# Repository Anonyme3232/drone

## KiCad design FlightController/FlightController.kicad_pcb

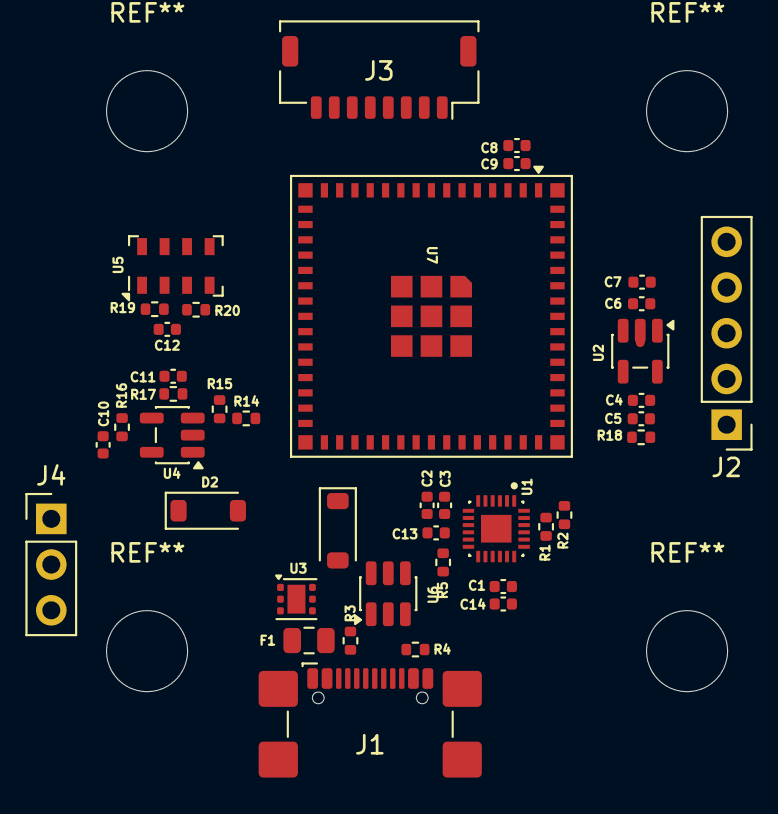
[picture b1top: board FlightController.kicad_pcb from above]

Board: 2 copper layers, 40 parts (0 on the bottom side), 31 nets.

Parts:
C1, C2: 10nF; C_0402_1005Metric
C3, C9, C13, C14: 100nF; C_0402_1005Metric
C4, C6: 1uF; C_0402_1005Metric
C5, C7, C8: 10uF; C_0402_1005Metric
C10: 22uF; C_0402_1005Metric
C11: 15nF; C_0402_1005Metric
C12: 0.1uF; C_0402_1005Metric
D1, D2: D_Schottky; D_SOD-123
F1: Polyfuse_Small; Fuse_0805_2012Metric
J1: USB_C_Receptacle_USB2.0_16P; USB_C_Receptacle_GCT_USB4110
J2: Conn_01x05; PinHeader_1x05_P2.54mm_Vertical
J3: Conn_01x08; JST_SHL_SM08B-SHLS-TF_1x08-1MP_P1.00mm_Horizontal
J4: Conn_01x03; PinHeader_1x03_P2.54mm_Vertical
R1, R2: 10k; R_0402_1005Metric
R3, R4, R18: 5.1K; R_0402_1005Metric
R5, R14, R15: 10K; R_0402_1005Metric
R16, R19, R20: 1K; R_0402_1005Metric
R17: 100K; R_0402_1005Metric
U1: MPU-6500; MPU6500
U2: AP2112K-3.3; SOT-23-5
U3: TVS0500DRV; WSON-6-1EP_2x2mm_P0.65mm_EP1x1.6mm
U4: MCP6001R; SOT-23-5
U5: MS5611-01BA; LGA-8_3x5mm_P1.25mm
U6: USBLC6-2SC6; SOT-23-6
U7: ESP32-S3-MINI-1U; ESP32-S2-MINI-1U

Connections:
/HB100/3V3: R14.1, U4.2 (V+)
/HB100/GPIO1: C11.2, R17.1, U4.1
/Raíz/3V3: C4.1, C5.1, C8.2, C9.2, C12.1, J2.1, R1.1, R2.1, R18.2, R19.1, U1.22 (NCS), U2.5 (VOUT), U5.1 (VDD), U7.3 (3V3)
/Raíz/5V: C6.1, C7.1, D1.1 (K), D2.1 (K), U2.1 (VIN), U2.3 (EN)
/Raíz/D+: U6.4 (I/O2), U7.24 (USB_D+)
/Raíz/D-: U6.6 (I/O1), U7.23 (USB_D-)
/Raíz/INT: R5.1, U1.12 (INT), U7.30 (IO48)
/Raíz/M1_R: J3.6, U7.19 (IO15)
/Raíz/M2_R: J3.5, U7.20 (IO16)
/Raíz/M3_R: J3.4, U7.21 (IO17)
/Raíz/M4_R: J3.3, U7.22 (IO18)
/Raíz/SCL: U5.8 (SCLK), U7.31 (IO35)
/Raíz/SDA: U5.7 (SDI/SDA), U7.32 (IO36)
/Raíz/VDDIO: C2.1, C3.2, U1.8 (VDDIO)
GND: C1.2, C2.2, C3.1, C4.2, C5.2, C6.2, C7.2, C8.1, C9.1, C12.2, C13.1, C14.1, F1.1, J1.A1 (GND), J1.A12 (GND), J1.B1 (GND), J1.B12 (GND), J1.SH (SHIELD), J2.4, J3.8, J4.3, R3.2, R4.2, R5.2, R15.1, R18.1, R20.2, U1.7 (AUX_CL), U1.9 (AD0/SDO), U1.11 (FSYNC), U1.18 (GND), U1.25 (EXP), U2.2 (GND), U3.1 (GND), U3.2 (GND), U3.3 (GND), U3.7 (GND), U4.5 (V-), U5.3 (GND), U6.2 (GND), U7.1 (GND), U7.2 (GND), U7.42 (GND), U7.43 (GND), U7.46 (GND), U7.47 (GND), U7.48 (GND), U7.49 (GND), U7.50 (GND), U7.51 (GND), U7.52 (GND), U7.53 (GND), U7.54 (GND), U7.55 (GND), U7.56 (GND), U7.57 (GND), U7.58 (GND), U7.59 (GND), U7.60 (GND), U7.61 (GND), U7.62 (GND), U7.63 (GND), U7.64 (GND), U7.65 (GND)
unnamed: C10.2, R16.1
unnamed: D1.2 (A), U3.4 (IN), U3.5 (IN), U3.6 (IN)
unnamed: F1.2, J1.A4 (VBUS), J1.A9 (VBUS), J1.B4 (VBUS), J1.B9 (VBUS)
unnamed: J1.A5 (CC1), R3.1
unnamed: J1.B5 (CC2), R4.1
unnamed: J1.A6 (D+), J1.B6 (D+), U6.3 (I/O2)
unnamed: J1.A7 (D-), J1.B7 (D-), U6.1 (I/O1)
unnamed: C10.1, J4.1
unnamed: R20.1, U5.4 (CSB), U5.5 (CSB)
unnamed: C13.2, U1.10 (REGOUT)
unnamed: R1.2, U1.23 (SCL/SCLK)
unnamed: R2.2, U1.24 (SDA/SDI)
unnamed: C1.1, C14.2, U1.13 (VDD)
unnamed: R14.2, R15.2, U4.3 (+)
unnamed: C11.1, R16.2, R17.2, U4.4 (-)
unnamed: R19.2, U5.2 (PS)

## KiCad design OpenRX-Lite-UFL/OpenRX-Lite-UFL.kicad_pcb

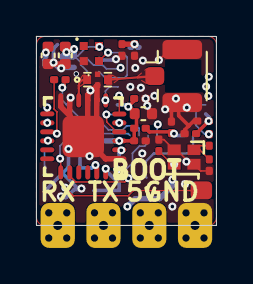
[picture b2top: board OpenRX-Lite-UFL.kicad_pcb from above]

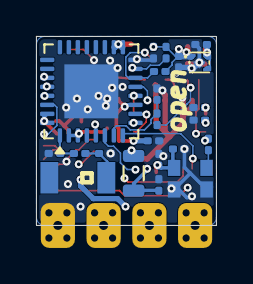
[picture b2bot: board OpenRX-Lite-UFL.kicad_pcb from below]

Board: 6 copper layers, 10.0 x 10.5 mm, 47 parts (22 on the bottom side), 28 nets.

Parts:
AE1: 2450AT18A100E; ANT-SMD_L3.2-W1.6
C1, C3: 15pF; C_0201_0603Metric
C4, C10, C15, C23, C25, C28: 1uF; C_0201_0603Metric
C5, C6, C9, C12, C13, C14, C17: 100nF; C_0201_0603Metric
C8, C11, C16: 10uF; C_0402_1005Metric
C19: 1nF; C_0201_0603Metric
C20: 470nF; C_0201_0603Metric
C21, C22: 1.2pF; C_0201_0603Metric
C24, C26, C27: 10nF; C_0201_0603Metric
D1: XL-1010RGBC-WS2812B; LED-SMD_4P-L1.0-W1.0-TL_XL-1010RGBC-WS2812B
FL1: 2450FM07D0034T; FILTER-SMD_4P-L1.0-W0.5-L
J1: Conn_Coaxial; U.FL_Hirose_U.FL-R-SMT-1_Vertical
L1: 24nH; L_0201_0603Metric
L2: 2.5nH; L_0201_0603Metric
L3: 2.0nH; L_0201_0603Metric
L4: 15uH; L_0805_2012Metric
OSC1: OW7EL89CENUNFAYLC-52M; OSC-SMD_4P-L2.0-W1.6-BL_TXC_7Z
R2, R3, R4, R5: 10k; R_0201_0603Metric
TP1: RX; SolderPad_1.2x2.0mm
TP2: TX; SolderPad_1.2x2.0mm
TP3: 5V; SolderPad_1.2x2.0mm
TP4: GND; SolderPad_1.2x2.0mm
TP5: BOOT; SolderPad_1.2x2.0mm
U1: ESP32-C3; QFN-32-1EP_5x5mm_P0.5mm_EP3.7x3.7mm
U2: TLV75533PDQNR; X2SON-4_L1.0-W1.0-P0.65-TL-EP
U3: SX1281IMLTRT; QFN-24_L4.0-W4.0-P0.50-TL-EP2.6
X1: CJ17-400001010B20; CRYSTAL-SMD_4P-L1.6-W1.2-BL

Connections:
+3V3: C4.1, C5.1, C6.1, C9.1, C11.1, C12.1, C13.1, C14.1, C15.1, C16.1, C17.1, C23.1, C24.1, D1.2 (VDD), L3.2, OSC1.4 (VDD), R2.1, R3.1, R4.1, R5.2, U1.11 (VDD3P3_RTC), U1.17 (VDD3P3_CPU), U1.18 (VDD_SPI), U1.31 (VDDA), U1.32 (VDDA), U2.1 (OUT), U3.11 (VBAT_IO), U3.15 (VBAT)
+5V: C8.1, C10.1, TP3.1 (1_1), U2.3 (EN), U2.4 (IN)
/ESP32-C3 + SX1281 Core (UFL)/BOOT: R4.2, TP5.1 (1_1), U1.15 (GPIO9)
/ESP32-C3 + SX1281 Core (UFL)/BUSY: U1.8 (GPIO3), U3.7 (BUSY)
/ESP32-C3 + SX1281 Core (UFL)/CHIP_EN: C28.1, R5.1, U1.7 (CHIP_EN)
/ESP32-C3 + SX1281 Core (UFL)/DIO1: U1.5 (XTAL_32K_N), U3.8 (DIO1)
/ESP32-C3 + SX1281 Core (UFL)/LED: D1.4 (DIN), R3.2, U1.14 (GPIO8)
/ESP32-C3 + SX1281 Core (UFL)/MISO: U1.10 (MTDI), U3.16 (MISO_TX)
/ESP32-C3 + SX1281 Core (UFL)/MOSI: U1.9 (MTMS), U3.17 (MOSI_RX)
/ESP32-C3 + SX1281 Core (UFL)/NSS: U1.13 (MTDO), U3.19 (NSS_CTS)
/ESP32-C3 + SX1281 Core (UFL)/RST: R2.2, U1.6 (GPIO2), U3.3 (NRESET)
/ESP32-C3 + SX1281 Core (UFL)/SCK: U1.12 (MTCK), U3.18 (SCK_RTSN)
/ESP32-C3 + SX1281 Core (UFL)/WIFI: AE1.1, C21.1, L2.1
/ESP32-C3 + SX1281 Core (UFL)/XTAL_N: C3.1, U1.29 (XTAL_N), X1.3
/ESP32-C3 + SX1281 Core (UFL)/XTAL_P: L1.2, U1.30 (XTAL_P)
GND: C1.2, C3.2, C4.2, C5.2, C6.2, C8.2, C9.2, C10.2, C11.2, C12.2, C13.2, C14.2, C15.2, C16.2, C17.2, C20.1, C21.2, C22.2, C23.2, C24.2, C25.2, C26.1, C27.2, C28.2, D1.3 (GND), FL1.2 (GND), FL1.4 (GND), J1.2 (Ext), OSC1.1 (GND), OSC1.2 (GND), TP4.1 (1_1), U1.16 (GPIO10), U1.33 (GND), U2.2 (GND), U2.5 (EP), U3.13 (GND), U3.20 (GND), U3.21 (GND), U3.23 (GND), U3.24 (GND), U3.25 (EP), X1.2 (GND), X1.4 (GND)
unnamed: C1.1, L1.1, X1.1
unnamed: C25.1, L3.1, U1.2 (VDD3P3), U1.3 (VDD3P3)
unnamed: FL1.1 (IN), U3.22 (RFIO)
unnamed: FL1.3 (OUT), J1.1 (In)
unnamed: C19.1, OSC1.3 (Out_Put)
unnamed: C22.1, L2.2, U1.1 (LNA_IN)
unnamed: TP1.1 (1_1), U1.27 (U0RXD)
unnamed: TP2.1 (1_1), U1.28 (U0TXD)
unnamed: C20.2, C26.2, L4.1, U3.2 (VDD_IN), U3.12 (DCC_FB)
unnamed: L4.2, U3.14 (DCC_SW)
unnamed: C27.1, U3.1 (VR_PA)
unnamed: C19.2, U3.4 (XTA)

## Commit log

2026-06-08 Descripción de tus cambios
2026-06-09 ACTUALIZACION
2026-06-13 ACTUALIZACION FC
